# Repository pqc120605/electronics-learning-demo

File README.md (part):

# Mạch Mở — demo học Điện tử, Nhúng và IoT

Mạch Mở là website học miễn phí cho người mới. Khách có thể xem bài học, khám phá mô hình mạch 3D tương tác và thử đổi nhịp LED trong bài ESP32 mà không cần tài khoản. Khu `/admin` dành cho founder để xem thống kê phiên truy cập và tương tác.

## Trang công khai và không gian học

- `/` là trang giới thiệu thế giới điện tử và các tính năng của Mạch Mở.
- `/app` là dashboard học tập dành cho khách, dẫn tới bài học, thư viện board/linh kiện, bàn lắp mạch, chủ đề, công cụ và dự án đang có.
- App workspace là một bề mặt guest-first chạy chung SPA React/Vite với website. Đây chưa phải native app. Service worker cache app shell cùng các JS/CSS đã tải để mở lại một số route khi offline; không cache model 3D lớn, firmware hay API, và chưa có đồng bộ offline.
- Bản đồ sản phẩm Web/App, ranh giới dữ liệu, simulator providers, công cụ GitHub đã khảo sát và lộ trình nền tảng được mô tả trong [`docs/mach-mo-final-web-app-framework.md`](../docs/mach-mo-final-web-app-framework.md).
- Route chuẩn nằm trong `src/data/productRoutes.ts`; feature, trạng thái và nhãn menu dùng chung nằm ở `src/data/productFeatureRegistry.ts`. URL legacy như `/boards` và `/build` vẫn được giữ để tương thích; các đường dẫn app có namespace `/app/...`.
- Hợp đồng chuẩn hóa cho simulation provider nằm tại `src/simulation/contracts.ts`. Các bài học dùng interpreter giáo dục giới hạn trong `src/lib/simulationProviders.ts`; công cụ SPICE dùng `eecircuit-engine`/ngspice WASM trong Web Worker. Workspace có handoff cho subset analog khi dây, node và trị số thỏa mapping hỗ trợ; compiler từ chối MCU/GPIO và phần tử chưa có model. Đây không phải chuyển đổi mọi bài/schematic, không lấy copper PCB làm netlist và không thay provider firmware.
- Luồng CAD có báo cáo đối chiếu tất cả chân có net trong KiCad schematic với PCB IPC-D-356 theo ref/pin và nhóm kết nối; giữ rõ chân NC và bỏ qua record via khi đếm chân. Sau đó, đường tạo netlist SPICE vẫn chỉ ánh xạ R/C/L/V hỗ trợ và yêu cầu loại trừ tường minh phần tử khác. Xem [hướng dẫn nhập KiCad vào SPICE](docs/kicad-to-spice-import.md); đối chiếu CAD không xác nhận file cùng revision hoặc board sản xuất, và PCB đơn lẻ không tự trở thành mô hình điện.
- Các URL chức năng hiện tại như `/learn/esp32-led`, `/boards`, `/components`, `/build`, `/topics`, `/projects` và `/tools/firmware-hex` vẫn dùng trực tiếp được.
- Dashboard `/app` và trang `/topics` hiển thị lộ trình 4 chặng gồm đủ 11 bài (`src/data/learningPath.ts`); bài LED mở trang dài `/learn/esp32-led`, 10 bài còn lại mở trang chuẩn bị `/learn/<id>` với mục tiêu, board, bảng chân, vật tư và mức mô phỏng trước khi vào phòng thử. Thứ tự này cũng quyết định "bài tiếp theo" trong phòng thử. Sơ đồ nguyên lý có danh sách net nối dây; chọn net tô sáng các kết nối tương ứng trên schematic và cảnh lắp. Net ở đây chỉ là topology workspace, không phải ERC, kết quả điện hay copper của PCB tham chiếu. Board profile hiển thị các link tài liệu/ảnh/CAD được khai báo cho đúng mẫu và revision; link nguồn là bằng chứng tham khảo, không xác minh board vật lý người học đang cầm. Bài vừa mở và checklist tự xác nhận của bài LED được lưu cục bộ; đây không phải tiến độ kỹ năng đã xác minh và không đồng bộ tài khoản.
- Cả 11 bài thực hành đều có deep link `?lesson=<id>`, ví dụ `/build?lesson=button-led&guided=1`; khi mở từ `/app`, liên kết nội bộ giữ namespace app. Link bài mở phiên riêng theo tab trong `sessionStorage`, tiếp tục bản nháp của phiên nếu có và không thay workspace `/build` trong `localStorage`. Link `?board=` chỉ đề xuất đổi board khi đã có workspace.
- Công cụ **Kiểm tra firmware HEX** đọc tệp Intel HEX ngay trong trình duyệt, kiểm tra checksum/địa chỉ/kích thước và hiển thị các vùng dữ liệu. Có firmware assembly mẫu và HEX do Arduino IDE 2.3.10 + Arduino AVR Boards 1.8.8 biên dịch từ sketch Uno; AVR8js cho chọn Uno R3 hoặc Nano classic, yêu cầu xác nhận target ATmega328P và chạy tối đa một giây để quan sát GPIO D13/PB5. Tệp người dùng chọn không tải lên máy chủ; target không nhận dạng tự động; web không compile sketch Arduino hay upload, và các board MCU khác chưa được hỗ trợ.
- Trong workspace `/build`, panel **Kết quả đến từ đâu?** phân biệt trace của mô hình bài học với lần chạy HEX AVR8js và waveform trả về từ SPICE. Chế độ HEX là tùy chọn riêng, chỉ nhận Uno R3/Nano classic ATmega328P sau khi người dùng xác nhận target; chỉ hiển thị D13/PB5 và UART0, không ánh xạ lên LED ngoài trên canvas. Kết quả SPICE chỉ quay lại cùng revision workspace trong phiên tab; sửa board, bài, code hoặc dây sẽ dừng/loại kết quả cũ. Đây là quan sát từ provider riêng, không phải đồng mô phỏng firmware–SPICE hay điện áp đo trên board.
- Web manifest cung cấp tên ứng dụng, màu giao diện, biểu tượng và điểm mở `/app`. Tùy trình duyệt và thiết bị, người dùng có thể cài website như một ứng dụng web.
- Cache offline hiện chỉ giữ app shell và tài nguyên cùng origin đã tải. Lần đầu cần có mạng để cài cache; engine SPICE lớn được tải khi mở/chạy công cụ và khả năng dùng offline phụ thuộc cache của trình duyệt. Chưa có tài khoản học viên hay chạy firmware MCU tổng quát.

## Chạy trên máy

Yêu cầu Node.js tương thích với Vite 8.

```powershell
cd D:\StartupOS\electronics-learning-demo
npm.cmd install
npm.cmd run dev -- --host 127.0.0.1 --port 5173 --strictPort --open /build
```

Lệnh luôn dùng `http://127.0.0.1:5173/build`; nếu cổng 5173 đang bận, Vite báo lỗi thay vì âm thầm chuyển sang cổng khác. Đóng cửa sổ terminal đang chạy một bản Mach Mở cũ rồi thử lại. Giữ terminal mở khi dùng web; dừng server bằng `Ctrl+C`.

Trên Windows, có thể chạy `start-demo.cmd` bằng cách nhấp đúp. Script dùng `npm.cmd` để tránh lỗi PowerShell chặn `npm.ps1`, rồi mở workspace `/build` ở cổng cố định. Giữ cửa sổ terminal mở trong lúc dùng; đóng server bằng `Ctrl+C`.

`npm.cmd run build` chạy cổng kiểm tra quyền phân phối trước khi tạo bản production; hiện sẽ bị chặn cho đến khi provenance của ngspice WASM được xác minh. Dùng `npm.cmd run build:local` chỉ để kiểm tra nội bộ; kết quả vẫn chứa WASM và không được phát hành hay tải lên hosting. Xem bản build nội bộ bằng `npm.cmd run preview`.

Kiểm tra kiểu bằng `npm.cmd run typecheck`. Chạy smoke test trước khi thay đổi curriculum, parser hoặc topology bằng `npm.cmd test`. Bộ test chạy qua Node test runner và Vite SSR, không cần cổng localhost; nó kiểm tra dữ liệu bài/board, code mẫu, topology preset của cả mười một bài, một số luật nối mạch và việc biên dịch các page module. Nó chưa tự thao tác UI trên trình duyệt.

Để rà model board, dùng `npm.cmd run audit:board-models` cho hotspot/anchor/scene bounds và `npm.cmd run audit:board-model-geometry` để so mesh thân PCB từ STEP đã ghim SHA-256 với node PCB tách riêng trong GLB (hiện có 8 cặp nguồn). Kết quả CAD-to-CAD không thay thế đo board thật. `npm.cmd run audit:spice-engine` kiểm tra hash/runtime và giải mạch DC mẫu; `npm.cmd run check:public-release` cố ý chặn cho tới khi đủ provenance, inventory và review phân phối ngspice WASM.

## Cấu hình Supabase riêng

Website này cần một Supabase project riêng. Không dùng project, URL, key hoặc dữ liệu của ReTrack. Nội dung học vẫn chạy nếu chưa cấu hình Supabase; khi chưa cấu hình, admin hiển thị hướng dẫn thiết lập và thống kê chưa khả dụng.

1. Tạo Supabase project dành riêng cho website.
2. Chạy lần lượt `supabase/migrations/0001_analytics_and_admin.sql` và `supabase/migrations/0002_analytics_rate_limit.sql` trong SQL Editor. Migration thứ hai thêm sự kiện chạy bài và giới hạn tốc độ theo mã phiên.
3. Trong Authentication → Settings, tắt đăng ký public. Trong Authentication → Users, tạo user founder với email và mật khẩu của bạn.
4. Lấy UUID của user trong Authentication → Users. Trong SQL Editor, cấp role admin cho đúng UUID:

   ```sql
   insert into public.site_admins (user_id)
   values ('DAN_UUID_USER_FOUNDER_VAO_DAY');
   ```

   Không thêm form đăng ký hoặc luồng tự cấp role vào website.
5. Sao chép `.env.example` thành `.env.local`, điền URL project và publishable/anon key. Chỉ dùng key công khai trong trình duyệt; không đưa service-role key vào `VITE_*` hay mã nguồn.
6. Khởi động lại dev server và mở `/admin` để đăng nhập.

Analytics chỉ ghi mã phiên ngẫu nhiên theo tab, loại sự kiện trong allowlist, đường dẫn, component tùy chọn và thời gian máy chủ. Số phiên là ước tính, không phải số người thật được xác minh. Nhà cung cấp backend có thể xử lý metadata kỹ thuật để vận hành.

## Giới hạn demo

- View "Lắp mạch · 3D" trong phòng thử dựng cảnh từ GLB thật, có chọn linh kiện, callout, panel thông tin và luồng logic minh họa. Nhãn HIGH/LOW và hướng lấy từ chương trình và sơ đồ bài học, không phải điện áp hay dòng đo được. Linh kiện giữ đúng tỉ lệ và được tự xếp lên breadboard; chỉ các chân cùng net mới chung một dải. Đây là cách lắp gợi ý, chưa kiểm tra trên mạch thật. Chân của model tham số và Pico là vị trí minh họa.

- Trang Linh kiện và phòng thử hiển thị minh họa/mesh 3D theo hồ sơ từng linh kiện; model package KiCad là vỏ chuẩn, còn model tham số chỉ là hình khối giáo dục. Board Adafruit QT Py ESP32-C3 Rev B #5405 và Feather ESP32-S3 PID #5323 có viewer CAD riêng theo nguồn hãng. Feather hiển thị cả footprint chưa có mesh và để các mesh không đối chiếu được ở trạng thái chưa định danh. Chi tiết, nguồn và giấy phép ở `docs/component-model-registry.md` và `docs/board-model-sourcing.md`.

- Bài ESP32 có hai cảnh 3D: PCB theo thiết kế ESP32 Dev Kit Clone 30 chân có schematic/netlist, và cảnh lắp mạch học tập gồm board, breadboard, LED, điện trở 220 Ω cùng dây jumper. Chọn linh kiện để xem vai trò, net/pad liên quan và lưu ý an toàn. Thiết kế này đo khoảng 47,06 × 29,23 mm; không đại diện cho mọi board bán dưới tên DevKit V1. Phần breadboard và linh kiện ngoài là hình học minh họa, không phải netlist hay mô phỏng điện.
- Viewer dùng WebGL2 và đọc profile GLB KiCad của asset mẫu. Mô hình chỉ thể hiện hình học, không mô phỏng điện áp/dòng điện hay chạy firmware. Hiệu ứng LED nhấp nháy trong viewer bài học chỉ là phản hồi hình ảnh.
- PCB, schematic, thông tin nguồn và hướng dẫn tái tạo model nằm trong `assets/boards/esp32-devkit-v1-30pin/`; GLB phục vụ web nằm trong `public/models/`. Sau khi xuất lại PCB GLB bằng KiCad, chạy `python assets/boards/esp32-devkit-v1-30pin/compose_led_assembly.py` để dựng lại cảnh lắp ráp. U3 CP2102 dùng vỏ QFN KiCad cùng kích thước, không có marking mặt chip.
- Web không biên dịch code hoặc nạp code qua USB. AVR8js là runner giới hạn cho ATmega328P trên Uno R3/Nano classic, nhận firmware HEX đã biên dịch và quan sát D13/ngoại vi cơ bản; không phải mô phỏng điện tổng quát hay hỗ trợ ESP32/Pico/STM32.
- Các model Arduino Uno/Nano/Mega trên web đã được thay bằng hình học PCB từ CAD board tham chiếu, kèm package 3D cho MCU, một số linh kiện thụ động, LED và header. CAD nguồn, attribution, giới hạn và cách xuất lại ở `assets/boards/arduino-reference/README.md`.
- Project chưa đọc được không bị xóa khi lưu; trang Dự án cho tải bản sao phục hồi. Kiểm kê asset và trạng thái Git nằm ở `docs/asset-and-repo-inventory.md`.
- Bản đầu chưa có tài khoản học viên, đồng bộ hoặc xác minh tiến độ học tập, thanh toán hay cửa hàng kit. Lịch sử bài vừa mở và checklist tự xác nhận, project và bản nháp workspace được lưu cục bộ trên thiết bị.
- Bài mẫu nêu rõ loại board và giả định chân GPIO; hãy đối chiếu pinout của board thực tế trước khi nối dây.

### Cách đọc mức độ mô phỏng và độ tin cậy

- **Mô phỏng hành vi cơ bản**: parser chỉ hiểu một tập câu lệnh được liệt kê trong bài. Nó chuyển code thuộc tập đó thành trạng thái/luồng minh họa; không biên dịch hay chạy firmware.
- **Minh họa khái niệm**: hoạt động theo kịch bản định sẵn; code mẫu không được thực thi.
- **Mô hình tham chiếu · CAD theo revision**: hình học được dựng từ bộ CAD/revision đã ghi nguồn. Nhãn này không xác nhận board clone đang bán có cùng layout, BOM hay linh kiện thực tế.
- **Alias học tập / suy luận từ CAD**: vị trí/chân hoặc package chưa được xác minh hoàn toàn. Các linh kiện rời trong bàn lắp có thể là hình học giáo dục tham số, không phải model nhà sản xuất.

Danh mục `/boards` ghi revision, nguồn và trạng thái viewer; `/components` phân biệt linh kiện có trong topology bài mẫu, chỉ hiển thị và chỉ tra cứu. Trang thư viện board và trang học hiển thị provenance của model: trạng thái, revision, nguồn, giấy phép/ghi công, độ tin cậy và các điểm còn thiếu. Không nên hiểu “có model 3D” là đã xác thực mọi linh kiện hoặc mô phỏng điện chính xác.

## Bộ công cụ

- `/tools/electronics-calculators` và `/app/tools/calculators`: bộ tính điện trở LED, bộ chia áp ADC, pull-up I²C và mạch RC. Mỗi kết quả hợp lệ có thể mở netlist tương đương trong SPICE. Trong workspace, tab **Schematic**, **Lắp mạch 3D** và **PCB** có thể gửi topology dây tường minh cùng R/C/LED/diode/LDR và trị số đã khai báo sang bộ biên dịch analog; yêu cầu GND, nguồn và các chân phải nối đủ. Board MCU, code/firmware, copper CAD, ký sinh PCB và linh kiện không có mapping đều bị loại hoặc chặn với lý do cụ thể. Đây là circuit subset theo topology workspace, không phải mô phỏng toàn board. Kết quả cần đối chiếu datasheet trước khi lắp thật.
- `/tools/spice` và `/app/tools/spice`: netlist analog chạy bằng ngspice WASM trong Web Worker của trình duyệt. Có ví dụ DC, RC transient, diode; netlist tối đa 16 kB/160 dòng, tối đa 20.000 điểm ước tính và giới hạn kết quả solver 20.000 điểm, timeout 30 giây; xem đồ thị/bảng và xuất CSV. Hỗ trợ có giới hạn R/C/L, V/I, diode/BJT/MOSFET với model số khai báo trực tiếp; chỉ `.op`, `.tran`, `.ac`, `.dc`. Ngoài handoff từ workspace, có thể nhập **XML netlist xuất từ KiCad Eeschema**: chỉ R/C/L và nguồn V DC có trị số tĩnh được giữ; linh kiện khác phải loại trừ bằng thao tác rõ ràng, nguồn/chân GND cần có. File `.kicad_sch`/`.kicad_pcb`, copper, parasitic, IC/MCU và firmware không tự chuyển đổi. Không nhận file/include/control, không chạy firmware MCU và không phải công cụ xác nhận an toàn/phần cứng. Engine WASM tải riêng khoảng 6,1 MB khi mở công cụ.
- Engine đóng gói từ `eecircuit-engine` 1.8.0; giấy phép MIT của wrapper được kèm ở `public/licenses/eecircuit-engine-MIT.txt`. **Quyền tái phân phối công khai của đúng ngspice WASM hiện chưa được xác minh**: source commit, build recipe và inventory thành phần linked còn thiếu dù artifact đang được phục vụ trong `public/`. Xem [provenance](public/licenses/spice-engine-provenance.json), [notice](public/licenses/NGSPICE-NOTICE.txt) và [ngspice COPYING](https://github.com/ngspice/ngspice/blob/master/COPYING).
- `postinstall` chạy `scripts/prepare-spice-engine.mjs`: tách WASM 6,1 MB khỏi bundle và bỏ các model-card foundry đóng gói sẵn mà giao diện không nhận qua `.include`. Các model người dùng khai báo trực tiếp trong netlist vẫn do solver xử lý. Script khóa phiên bản engine 1.8.0 và dừng nếu cấu trúc upstream thay đổi; license và thông báo của package vẫn được giữ.
- `/app/classroom-kits`: kế hoạch lớp/kit cục bộ, chọn board và revision tham chiếu, 1–100 trạm, bài học, số lượng kit, lưu ý an toàn, in phiếu, xuất CSV/JSON và nhập lại gói đã kiểm tra allowlist. Gói chia sẻ thủ công kèm link bài, nhãn năng lực mô phỏng, thông tin board/revision, nguồn board và ghi chú an toàn; chưa có upload/cloud, tài khoản lớp, bảng tin hay kiểm duyệt cộng đồng. Không thu dữ liệu học sinh.

## Thư viện board và bài học lập trình

- Trang Khám phá có tìm kiếm và lọc theo ESP, Arduino, STM32; có thể chọn tối đa ba board để so sánh MCU, revision, điện áp logic, ngoại vi, mục tiêu phù hợp, điểm đánh đổi và trạng thái model. Bảng cảnh báo khi mức logic khác nhau, có link nguồn, bỏ từng board và xóa lựa chọn. Thông tin preview luôn đi kèm nguồn và trạng thái xác minh.
- Bài LED có chế độ khối cho người mới, tạo code C++ từ các khối GPIO/chờ, và chế độ C++ riêng để tự luyện. Bản nháp code được giữ khi đổi chế độ; chỉ cú pháp thuộc tập con được hỗ trợ mới chuyển thành luồng minh họa. Cú pháp khác được giữ nguyên và tắt luồng, không chạy code trong trình duyệt.
- Luồng hoạt động chỉ minh họa câu lệnh, GPIO và trạng thái LED theo từng bước; không mô phỏng firmware, điện học hoặc thời gian thực.
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
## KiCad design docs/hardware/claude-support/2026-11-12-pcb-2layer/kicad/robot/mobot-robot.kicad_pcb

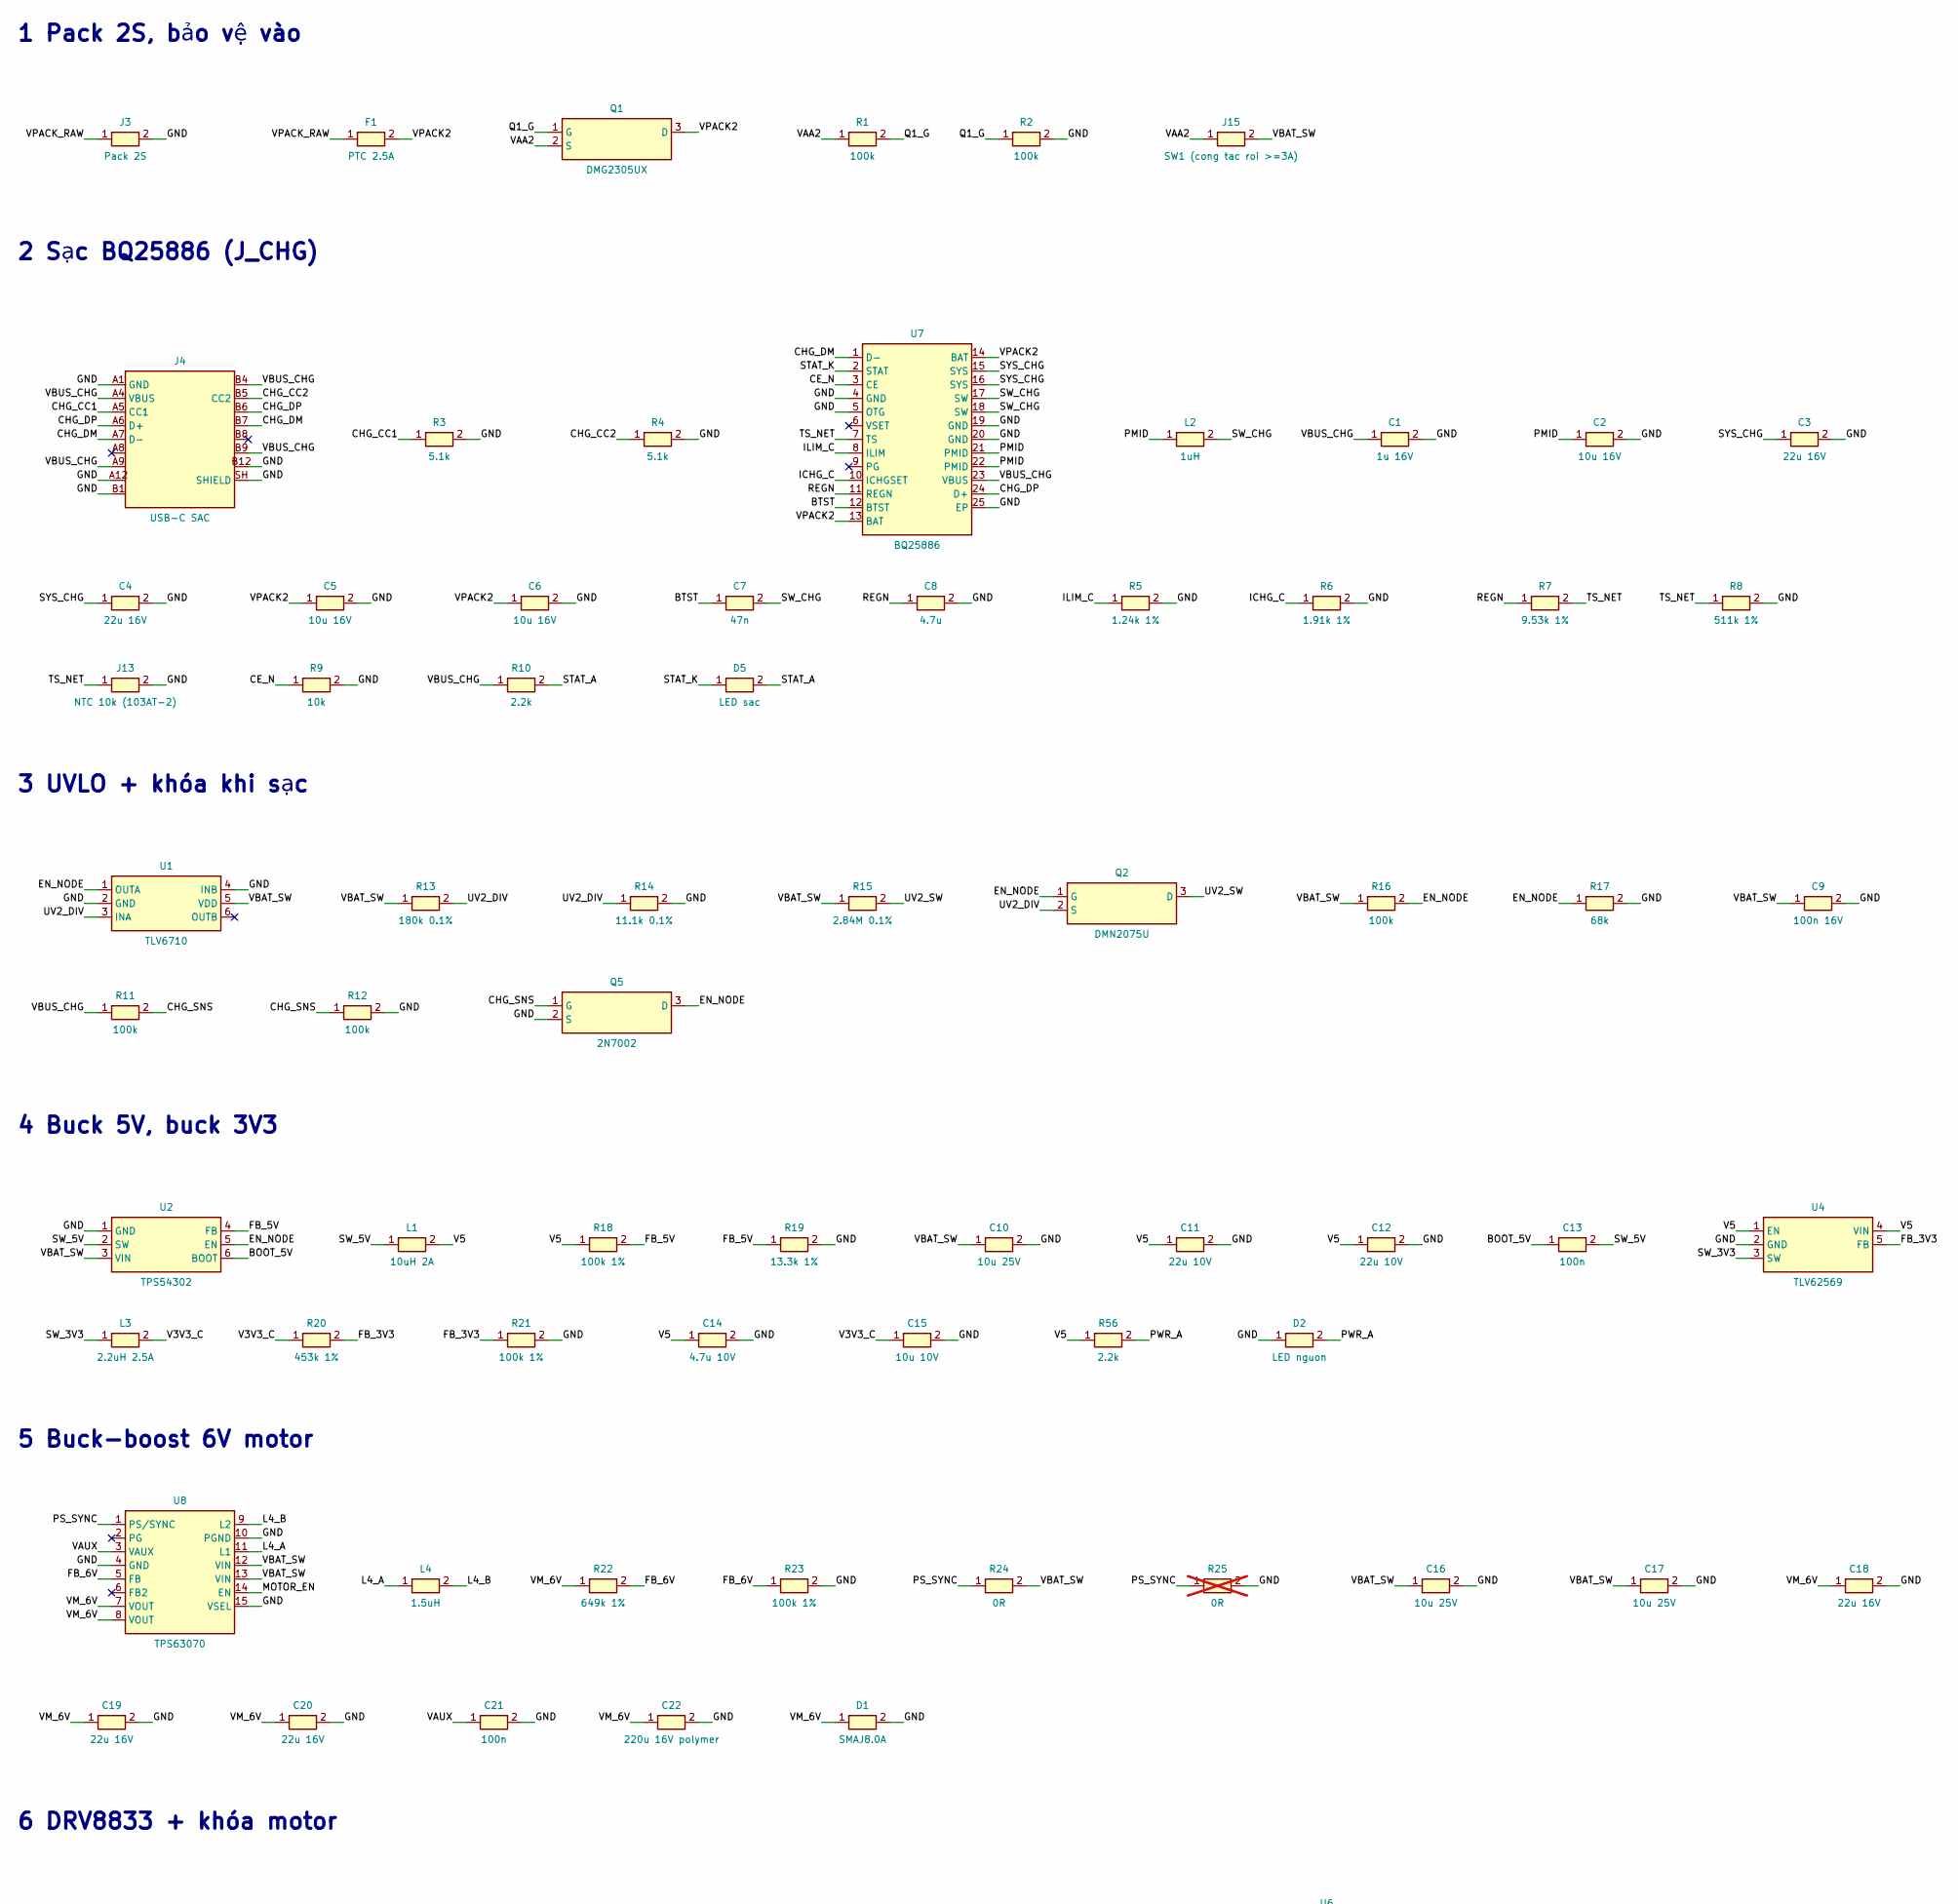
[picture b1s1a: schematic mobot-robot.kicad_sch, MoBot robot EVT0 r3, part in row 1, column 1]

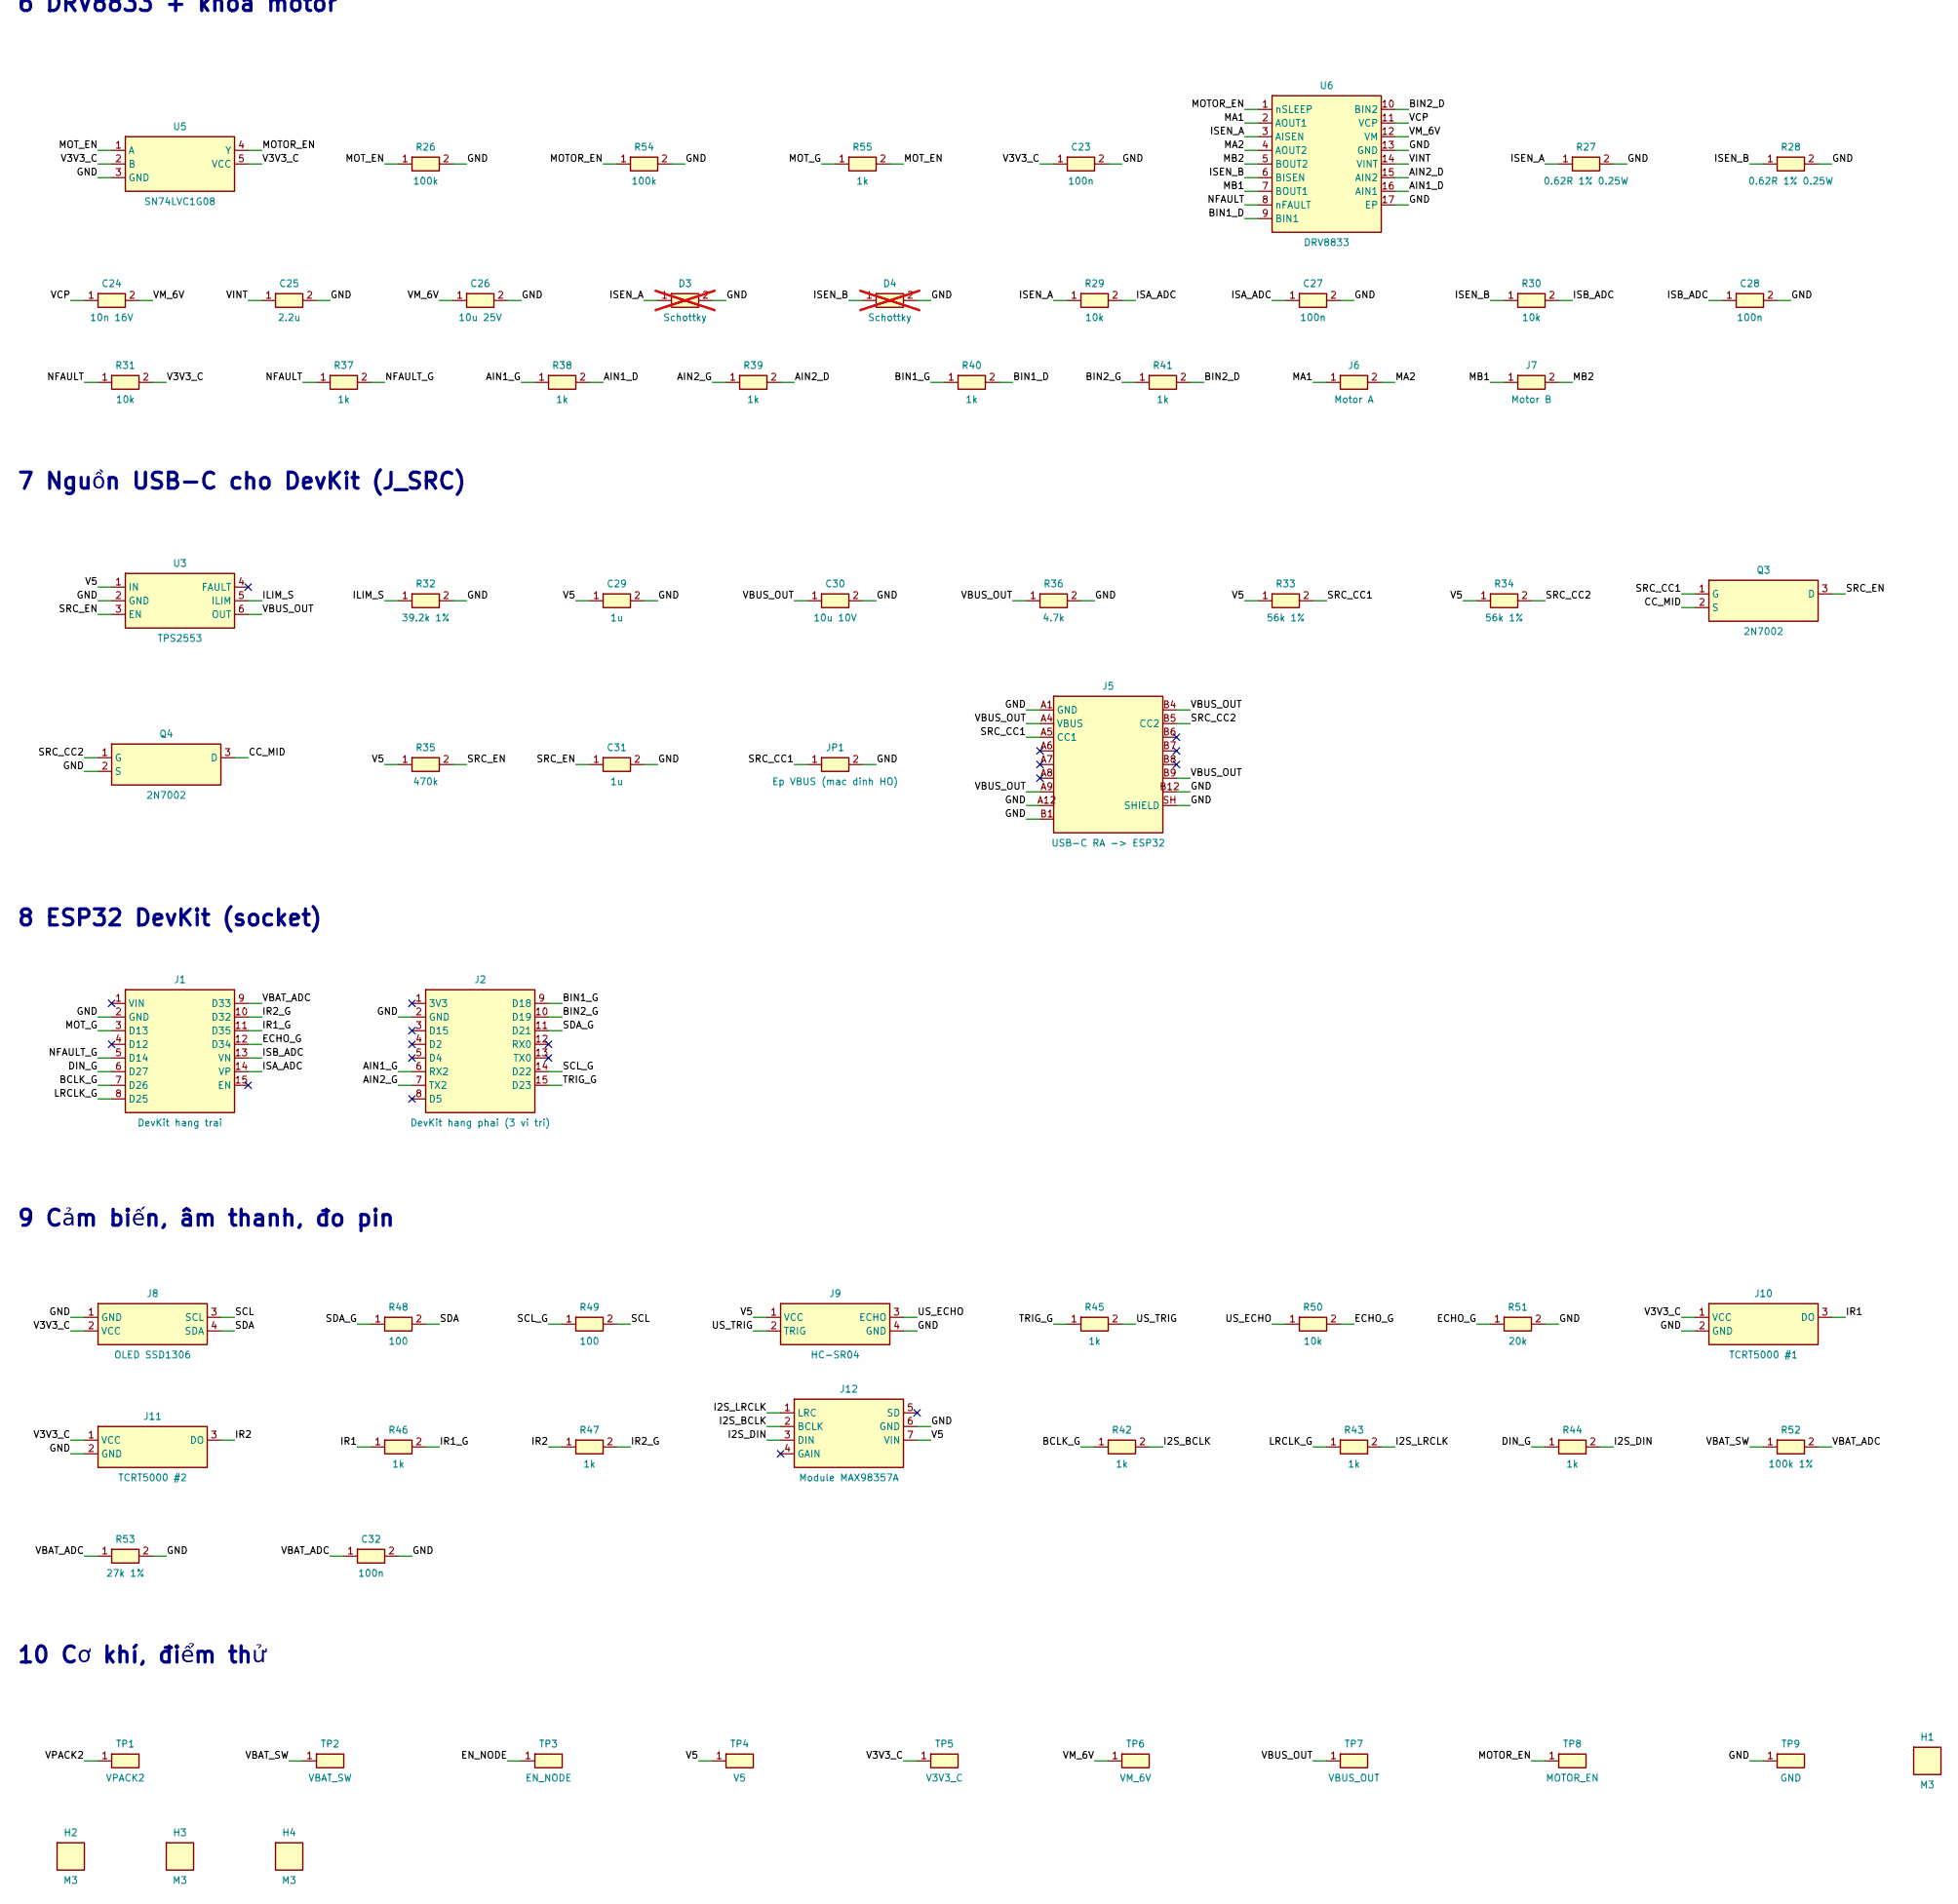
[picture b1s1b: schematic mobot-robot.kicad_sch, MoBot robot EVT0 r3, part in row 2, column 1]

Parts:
C1: 1u 16V; C_0603_1608Metric
C2, C5, C6: 10u 16V; C_0805_2012Metric
C3, C4, C18, C19, C20: 22u 16V; C_0805_2012Metric
C7: 47n; C_0603_1608Metric
C8: 4.7u; C_0603_1608Metric
C9: 100n 16V; C_0603_1608Metric
C10, C16, C17, C26: 10u 25V; C_0805_2012Metric
C11, C12: 22u 10V; C_0805_2012Metric
C13, C21, C23, C27, C28, C32: 100n; C_0603_1608Metric
C14: 4.7u 10V; C_0805_2012Metric
C15, C30: 10u 10V; C_0805_2012Metric
C22: 220u 16V polymer; CP_Elec_8x10
C24: 10n 16V; C_0603_1608Metric
C25: 2.2u; C_0603_1608Metric
C29, C31: 1u; C_0603_1608Metric
D1: SMAJ8.0A; D_SMA; MPN SMAJ8.0A
D2: LED nguon; LED_0603_1608Metric
D3, D4: Schottky; D_SOD-323; not fitted
D5: LED sac; LED_0603_1608Metric
F1: PTC 2.5A; Fuse_1812_4532Metric; MPN MF-MSMF250/16X
H1, H2, H3, H4: M3; MountingHole_3.2mm_M3
J1: DevKit hang trai; PinSocket_1x15_P2.54mm_Vertical
J2: DevKit hang phai (3 vi tri); PinSocket_1x15_Alt3Rows_22.86_25.40_27.94
J3: Pack 2S; JST_XH_B2B-XH-A_1x02_P2.50mm_Vertical; MPN B2B-XH-A
J4: USB-C SAC; USB_C_Receptacle_GCT_USB4105-xx-A_16P_TopMnt_Horizontal; MPN USB4105-GF-A
J5: USB-C RA -> ESP32; USB_C_Receptacle_GCT_USB4105-xx-A_16P_TopMnt_Horizontal; MPN USB4105-GF-A
J6: Motor A; JST_XH_B2B-XH-A_1x02_P2.50mm_Vertical; MPN B2B-XH-A
J7: Motor B; JST_XH_B2B-XH-A_1x02_P2.50mm_Vertical; MPN B2B-XH-A
J8: OLED SSD1306; PinSocket_1x04_P2.54mm_Vertical
J9: HC-SR04; PinSocket_1x04_P2.54mm_Vertical
J10: TCRT5000 #1; PinHeader_1x03_P2.54mm_Vertical
J11: TCRT5000 #2; PinHeader_1x03_P2.54mm_Vertical
J12: Module MAX98357A; PinSocket_1x07_P2.54mm_Vertical
J13: NTC 10k (103AT-2); JST_PH_B2B-PH-K_1x02_P2.00mm_Vertical; MPN B2B-PH-K-S
J15: SW1 (cong tac roi >=3A); JST_XH_B2B-XH-A_1x02_P2.50mm_Vertical; MPN B2B-XH-A
JP1: Ep VBUS (mac dinh HO); SolderJumper-2_P1.3mm_Open_RoundedPad1.0x1.5mm
L1: 10uH 2A; L_Taiyo-Yuden_NR-50xx
L2: 1uH; L_Vishay_IHLP-2525; MPN IHLP2525CZER1R0M01
L3: 2.2uH 2.5A; L_Changjiang_FNR4030S
L4: 1.5uH; L_Changjiang_FNR4020S; MPN XFL4020-152ME
Q1: DMG2305UX; SOT-23; MPN DMG2305UX-7
Q2: DMN2075U; SOT-23; MPN DMN2075U-7
Q3, Q4, Q5: 2N7002; SOT-23; MPN 2N7002
R1, R2, R11, R12, R16, R26, R54: 100k; R_0603_1608Metric
R3, R4: 5.1k; R_0603_1608Metric
R5: 1.24k 1%; R_0603_1608Metric
R6: 1.91k 1%; R_0603_1608Metric
R7: 9.53k 1%; R_0603_1608Metric
R8: 511k 1%; R_0603_1608Metric
R9, R29, R30, R31, R50: 10k; R_0603_1608Metric
R10, R56: 2.2k; R_0603_1608Metric
R13: 180k 0.1%; R_0603_1608Metric
R14: 11.1k 0.1%; R_0603_1608Metric
R15: 2.84M 0.1%; R_0603_1608Metric
R17: 68k; R_0603_1608Metric
R18, R21, R23, R52: 100k 1%; R_0603_1608Metric
R19: 13.3k 1%; R_0603_1608Metric
R20: 453k 1%; R_0603_1608Metric
R22: 649k 1%; R_0603_1608Metric
R24: 0R; R_0603_1608Metric
R25: 0R; R_0603_1608Metric; not fitted
R27, R28: 0.62R 1% 0.25W; R_1206_3216Metric
R32: 39.2k 1%; R_0603_1608Metric
R33, R34: 56k 1%; R_0603_1608Metric
R35: 470k; R_0603_1608Metric
R36: 4.7k; R_0603_1608Metric
R37, R38, R39, R40, R41, R42, R43, R44, R45, R46, R47, R55: 1k; R_0603_1608Metric
R48, R49: 100; R_0603_1608Metric
R51: 20k; R_0603_1608Metric
R53: 27k 1%; R_0603_1608Metric
TP1: VPACK2; TestPoint_Pad_D1.5mm
TP2: VBAT_SW; TestPoint_Pad_D1.5mm
TP3: EN_NODE; TestPoint_Pad_D1.5mm
TP4: V5; TestPoint_Pad_D1.5mm
TP5: V3V3_C; TestPoint_Pad_D1.5mm
TP6: VM_6V; TestPoint_Pad_D1.5mm
TP7: VBUS_OUT; TestPoint_Pad_D1.5mm
TP8: MOTOR_EN; TestPoint_Pad_D1.5mm
TP9: GND; TestPoint_Pad_D1.5mm
U1: TLV6710; TSOT-23-6; MPN TLV6710DDCR
U2: TPS54302; SOT-23-6; MPN TPS54302DDCR
U3: TPS2553; SOT-23-6; MPN TPS2553DBVR
U4: TLV62569; SOT-23-5; MPN TLV62569DBVR
U5: SN74LVC1G08; SOT-23-5; MPN SN74LVC1G08DBVR
U6: DRV8833; HTSSOP-16-1EP_4.4x5mm_P0.65mm_EP3.4x5mm_Mask2.46x2.31mm_The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; MPN DRV8833PWPR
U7: BQ25886; VQFN-24-1EP_4x4mm_P0.5mm_EP2.45x2.45mm; MPN BQ25886RGER
U8: TPS63070; Texas_RNM0015A_VQFN-15_2.5x3mm; MPN TPS63070RNMR

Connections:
/AIN1_D: R38.2, U6.16 (AIN1)
/AIN1_G: J2.6 (RX2), R38.1
/AIN2_D: R39.2, U6.15 (AIN2)
/AIN2_G: J2.7 (TX2), R39.1
/BCLK_G: J1.7 (D26), R42.1
/BIN1_D: R40.2, U6.9 (BIN1)
/BIN1_G: J2.9 (D18), R40.1
/BIN2_D: R41.2, U6.10 (BIN2)
/BIN2_G: J2.10 (D19), R41.1
/BOOT_5V: C13.1, U2.6 (BOOT)
/BTST: C7.1, U7.12 (BTST)
/CC_MID: Q3.2 (S), Q4.3 (D)
/CE_N: R9.1, U7.3 (CE)
/CHG_CC1: J4.A5 (CC1), R3.1
/CHG_CC2: J4.B5 (CC2), R4.1
/CHG_DM: J4.A7 (D-), J4.B7, U7.1 (D-)
/CHG_DP: J4.A6 (D+), J4.B6, U7.24 (D+)
/CHG_SNS: Q5.1 (G), R11.2, R12.1
/DIN_G: J1.6 (D27), R44.1
/ECHO_G: J1.12 (D34), R50.2, R51.1
/EN_NODE: Q2.1 (G), Q5.3 (D), R16.2, R17.1, TP3.1, U1.1 (OUTA), U2.5 (EN)
/FB_3V3: R20.2, R21.1, U4.5 (FB)
/FB_5V: R18.2, R19.1, U2.4 (FB)
/FB_6V: R22.2, R23.1, U8.5 (FB)
/GND: C1.2, C2.2, C3.2, C4.2, C5.2, C6.2, C8.2, C9.2, C10.2, C11.2, C12.2, C14.2, C15.2, C16.2, C17.2, C18.2, C19.2, C20.2, C21.2, C22.2 (-), C23.2, C25.2, C26.2, C27.2, C28.2, C29.2, C30.2, C31.2, C32.2, D1.2 (A), D2.1 (K), D3.2 (A), D4.2 (A), J1.2 (GND), J2.2 (GND), J3.2 (-), J4.A1 (GND), J4.A12, J4.B1, J4.B12, J4.SH (SHIELD), J5.A1 (GND), J5.A12, J5.B1, J5.B12, J5.SH (SHIELD), J8.1 (GND), J9.4 (GND), J10.2 (GND), J11.2 (GND), J12.6 (GND), J13.2, JP1.2, Q4.2 (S), Q5.2 (S), R2.2, R3.2, R4.2, R5.2, R6.2, R8.2, R9.2, R12.2, R14.2, R17.2, R19.2, R21.2, R23.2, R25.2, R26.2, R27.2, R28.2, R32.2, R36.2, R51.2, R53.2, R54.2, TP9.1, U1.2 (GND), U1.4 (INB), U2.1 (GND), U3.2 (GND), U4.2 (GND), U5.3 (GND), U6.13 (GND), U6.17 (EP), U7.4 (GND), U7.5 (OTG), U7.19 (GND), U7.20 (GND), U7.25 (EP), U8.4 (GND), U8.10 (PGND), U8.15 (VSEL)
/I2S_BCLK: J12.2 (BCLK), R42.2
/I2S_DIN: J12.3 (DIN), R44.2
/I2S_LRCLK: J12.1 (LRC), R43.2
/ICHG_C: R6.1, U7.10 (ICHGSET)
/ILIM_C: R5.1, U7.8 (ILIM)
/ILIM_S: R32.1, U3.5 (ILIM)
/IR1: J10.3 (DO), R46.1
/IR1_G: J1.11 (D35), R46.2
/IR2: J11.3 (DO), R47.1
/IR2_G: J1.10 (D32), R47.2
/ISA_ADC: C27.1, J1.14 (VP), R29.2
/ISB_ADC: C28.1, J1.13 (VN), R30.2
/ISEN_A: D3.1 (K), R27.1, R29.1, U6.3 (AISEN)
/ISEN_B: D4.1 (K), R28.1, R30.1, U6.6 (BISEN)
/L4_A: L4.1, U8.11 (L1)
/L4_B: L4.2, U8.9 (L2)
/LRCLK_G: J1.8 (D25), R43.1
/MA1: J6.1, U6.2 (AOUT1)
/MA2: J6.2, U6.4 (AOUT2)
/MB1: J7.1, U6.7 (BOUT1)
/MB2: J7.2, U6.5 (BOUT2)
/MOTOR_EN: R54.1, TP8.1, U5.4 (Y), U6.1 (nSLEEP), U8.14 (EN)
/MOT_EN: R26.1, R55.2, U5.1 (A)
/MOT_G: J1.3 (D13), R55.1
/NFAULT: R31.1, R37.1, U6.8 (nFAULT)
/NFAULT_G: J1.5 (D14), R37.2
/PMID: C2.1, L2.1, U7.21 (PMID), U7.22 (PMID)
/PS_SYNC: R24.1, R25.1, U8.1 (PS/SYNC)
/PWR_A: D2.2 (A), R56.2
/Q1_G: Q1.1 (G), R1.2, R2.1
/REGN: C8.1, R7.1, U7.11 (REGN)
/SCL: J8.3 (SCL), R49.2
/SCL_G: J2.14 (D22), R49.1
/SDA: J8.4 (SDA), R48.2
/SDA_G: J2.11 (D21), R48.1
/SRC_CC1: J5.A5 (CC1), JP1.1, Q3.1 (G), R33.2
/SRC_CC2: J5.B5 (CC2), Q4.1 (G), R34.2
/SRC_EN: C31.1, Q3.3 (D), R35.2, U3.3 (EN)
/STAT_A: D5.2 (A), R10.2
/STAT_K: D5.1 (K), U7.2 (STAT)
/SW_3V3: L3.1, U4.3 (SW)
/SW_5V: C13.2, L1.1, U2.2 (SW)
/SW_CHG: C7.2, L2.2, U7.17 (SW), U7.18 (SW)
/SYS_CHG: C3.1, C4.1, U7.15 (SYS), U7.16 (SYS)
/TRIG_G: J2.15 (D23), R45.1
/TS_NET: J13.1, R7.2, R8.1, U7.7 (TS)
/US_ECHO: J9.3 (ECHO), R50.1
/US_TRIG: J9.2 (TRIG), R45.2
/UV2_DIV: Q2.2 (S), R13.2, R14.1, U1.3 (INA)
/UV2_SW: Q2.3 (D), R15.2
/V3V3_C: C15.1, C23.1, J8.2 (VCC), J10.1 (VCC), J11.1 (VCC), L3.2, R20.1, R31.2, TP5.1, U5.2 (B), U5.5 (VCC)
/V5: C11.1, C12.1, C14.1, C29.1, J9.1 (VCC), J12.7 (VIN), L1.2, R18.1, R33.1, R34.1, R35.1, R56.1, TP4.1, U3.1 (IN), U4.1 (EN), U4.4 (VIN)
/VAA2: J15.1 (IN), Q1.2 (S), R1.1
/VAUX: C21.1, U8.3 (VAUX)
/VBAT_ADC: C32.1, J1.9 (D33), R52.2, R53.1
/VBAT_SW: C9.1, C10.1, C16.1, C17.1, J15.2 (OUT), R13.1, R15.1, R16.1, R24.2, R52.1, TP2.1, U1.5 (VDD), U2.3 (VIN), U8.12 (VIN), U8.13 (VIN)
/VBUS_CHG: C1.1, J4.A4 (VBUS), J4.A9, J4.B4, J4.B9, R10.1, R11.1, U7.23 (VBUS)
/VBUS_OUT: C30.1, J5.A4 (VBUS), J5.A9, J5.B4, J5.B9, R36.1, TP7.1, U3.6 (OUT)
/VCP: C24.1, U6.11 (VCP)
/VINT: C25.1, U6.14 (VINT)
/VM_6V: C18.1, C19.1, C20.1, C22.1 (+), C24.2, C26.1, D1.1 (K), R22.1, TP6.1, U6.12 (VM), U8.7 (VOUT), U8.8 (VOUT)
/VPACK2: C5.1, C6.1, F1.2, Q1.3 (D), TP1.1, U7.13 (BAT), U7.14 (BAT)
/VPACK_RAW: F1.1, J3.1 (+)

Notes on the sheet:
1 Pack 2S, bảo vệ vào
2 Sạc BQ25886 (J_CHG)
3 UVLO + khóa khi sạc
4 Buck 5V, buck 3V3
5 Buck-boost 6V motor
6 DRV8833 + khóa motor
7 Nguồn USB-C cho DevKit (J_SRC)
8 ESP32 DevKit (socket)
9 Cảm biến, âm thanh, đo pin
10 Cơ khí, điểm thử

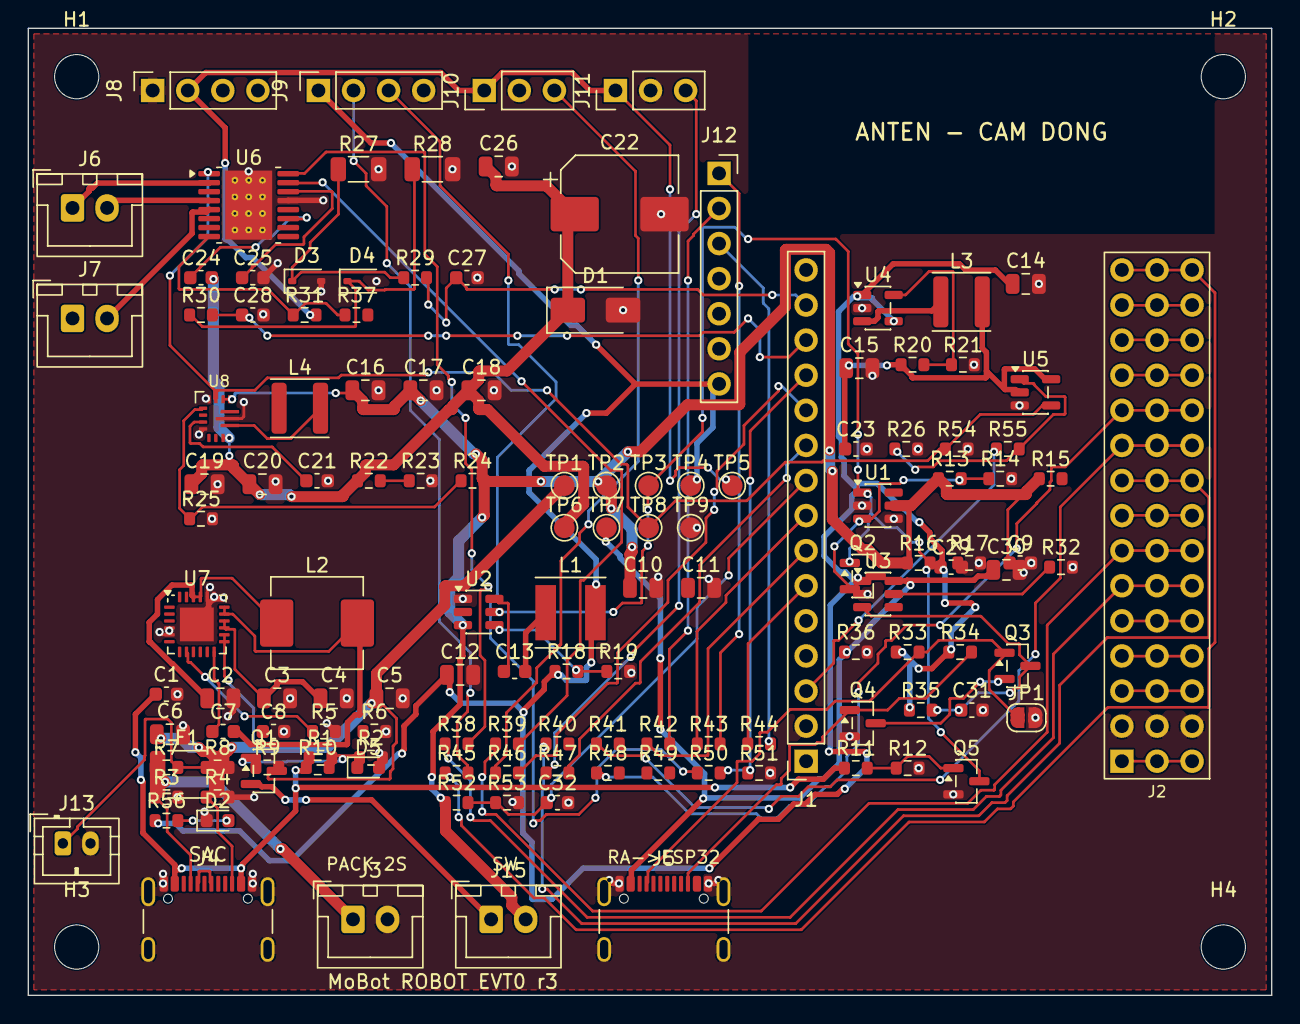
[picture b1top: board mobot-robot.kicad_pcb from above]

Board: 2 copper layers, 90.0 x 70.0 mm, 139 parts (0 on the bottom side), 88 nets.

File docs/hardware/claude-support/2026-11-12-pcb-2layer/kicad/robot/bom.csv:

"Ref","Value","Footprint","MPN","Qty","DNP"
"C1","1u 16V","Capacitor_SMD:C_0603_1608Metric","","1",""
"C2,C5,C6","10u 16V","Capacitor_SMD:C_0805_2012Metric","","3",""
"C3,C4,C18-C20","22u 16V","Capacitor_SMD:C_0805_2012Metric","","5",""
"C7","47n","Capacitor_SMD:C_0603_1608Metric","","1",""
"C8","4.7u","Capacitor_SMD:C_0603_1608Metric","","1",""
"C9","100n 16V","Capacitor_SMD:C_0603_1608Metric","","1",""
"C10,C16,C17,C26","10u 25V","Capacitor_SMD:C_0805_2012Metric","","4",""
"C11,C12","22u 10V","Capacitor_SMD:C_0805_2012Metric","","2",""
"C13,C21,C23,C27,C28,C32","100n","Capacitor_SMD:C_0603_1608Metric","","6",""
"C14","4.7u 10V","Capacitor_SMD:C_0805_2012Metric","","1",""
"C15,C30","10u 10V","Capacitor_SMD:C_0805_2012Metric","","2",""
"C22","220u 16V polymer","Capacitor_SMD:CP_Elec_8x10","","1",""
"C24","10n 16V","Capacitor_SMD:C_0603_1608Metric","","1",""
"C25","2.2u","Capacitor_SMD:C_0603_1608Metric","","1",""
"C29,C31","1u","Capacitor_SMD:C_0603_1608Metric","","2",""
"D1","SMAJ8.0A","Diode_SMD:D_SMA","SMAJ8.0A","1",""
"D2","LED nguon","LED_SMD:LED_0603_1608Metric","","1",""
"D3,D4","Schottky","Diode_SMD:D_SOD-323","","2","DNP"
"D5","LED sac","LED_SMD:LED_0603_1608Metric","","1",""
"F1","PTC 2.5A","Fuse:Fuse_1812_4532Metric","MF-MSMF250/16X","1",""
"J1","DevKit hang trai","Connector_PinSocket_2.54mm:PinSocket_1x15_P2.54mm_Vertical","","1",""
"J2","DevKit hang phai (3 vi tri)","mobot:PinSocket_1x15_Alt3Rows_22.86_25.40_27.94","","1",""
"J3","Pack 2S","Connector_JST:JST_XH_B2B-XH-A_1x02_P2.50mm_Vertical","B2B-XH-A","1",""
"J4","USB-C SAC","Connector_USB:USB_C_Receptacle_GCT_USB4105-xx-A_16P_TopMnt_Horizontal","USB4105-GF-A","1",""
"J5","USB-C RA -> ESP32","Connector_USB:USB_C_Receptacle_GCT_USB4105-xx-A_16P_TopMnt_Horizontal","USB4105-GF-A","1",""
"J6","Motor A","Connector_JST:JST_XH_B2B-XH-A_1x02_P2.50mm_Vertical","B2B-XH-A","1",""
"J7","Motor B","Connector_JST:JST_XH_B2B-XH-A_1x02_P2.50mm_Vertical","B2B-XH-A","1",""
"J8","OLED SSD1306","Connector_PinSocket_2.54mm:PinSocket_1x04_P2.54mm_Vertical","","1",""
"J9","HC-SR04","Connector_PinSocket_2.54mm:PinSocket_1x04_P2.54mm_Vertical","","1",""
"J10","TCRT5000 #1","Connector_PinHeader_2.54mm:PinHeader_1x03_P2.54mm_Vertical","","1",""
"J11","TCRT5000 #2","Connector_PinHeader_2.54mm:PinHeader_1x03_P2.54mm_Vertical","","1",""
"J12","Module MAX98357A","Connector_PinSocket_2.54mm:PinSocket_1x07_P2.54mm_Vertical","","1",""
"J13","NTC 10k (103AT-2)","Connector_JST:JST_PH_B2B-PH-K_1x02_P2.00mm_Vertical","B2B-PH-K-S","1",""
"J15","SW1 (cong tac roi >=3A)","Connector_JST:JST_XH_B2B-XH-A_1x02_P2.50mm_Vertical","B2B-XH-A","1",""
"L1","10uH 2A","Inductor_SMD:L_Taiyo-Yuden_NR-50xx","","1",""
"L2","1uH","Inductor_SMD:L_Vishay_IHLP-2525","IHLP2525CZER1R0M01","1",""
"L3","2.2uH 2.5A","Inductor_SMD:L_Changjiang_FNR4030S","","1",""
"L4","1.5uH","Inductor_SMD:L_Changjiang_FNR4020S","XFL4020-152ME","1",""
"Q1","DMG2305UX","Package_TO_SOT_SMD:SOT-23","DMG2305UX-7","1",""
"Q2","DMN2075U","Package_TO_SOT_SMD:SOT-23","DMN2075U-7","1",""
"Q3-Q5","2N7002","Package_TO_SOT_SMD:SOT-23","2N7002","3",""
"R1,R2,R11,R12,R16,R26,R54","100k","Resistor_SMD:R_0603_1608Metric","","7",""
"R3,R4","5.1k","Resistor_SMD:R_0603_1608Metric","","2",""
"R5","1.24k 1%","Resistor_SMD:R_0603_1608Metric","","1",""
"R6","1.91k 1%","Resistor_SMD:R_0603_1608Metric","","1",""
"R7","9.53k 1%","Resistor_SMD:R_0603_1608Metric","","1",""
"R8","511k 1%","Resistor_SMD:R_0603_1608Metric","","1",""
"R9,R29-R31,R50","10k","Resistor_SMD:R_0603_1608Metric","","5",""
"R10,R56","2.2k","Resistor_SMD:R_0603_1608Metric","","2",""
"R13","180k 0.1%","Resistor_SMD:R_0603_1608Metric","","1",""
"R14","11.1k 0.1%","Resistor_SMD:R_0603_1608Metric","","1",""
"R15","2.84M 0.1%","Resistor_SMD:R_0603_1608Metric","","1",""
"R17","68k","Resistor_SMD:R_0603_1608Metric","","1",""
"R18,R21,R23,R52","100k 1%","Resistor_SMD:R_0603_1608Metric","","4",""
"R19","13.3k 1%","Resistor_SMD:R_0603_1608Metric","","1",""
"R20","453k 1%","Resistor_SMD:R_0603_1608Metric","","1",""
"R22","649k 1%","Resistor_SMD:R_0603_1608Metric","","1",""
"R24","0R","Resistor_SMD:R_0603_1608Metric","","1",""
"R25","0R","Resistor_SMD:R_0603_1608Metric","","1","DNP"
"R27,R28","0.62R 1% 0.25W","Resistor_SMD:R_1206_3216Metric","","2",""
"R32","39.2k 1%","Resistor_SMD:R_0603_1608Metric","","1",""
"R33,R34","56k 1%","Resistor_SMD:R_0603_1608Metric","","2",""
"R35","470k","Resistor_SMD:R_0603_1608Metric","","1",""
"R36","4.7k","Resistor_SMD:R_0603_1608Metric","","1",""
"R37-R47,R55","1k","Resistor_SMD:R_0603_1608Metric","","12",""
"R48,R49","100","Resistor_SMD:R_0603_1608Metric","","2",""
"R51","20k","Resistor_SMD:R_0603_1608Metric","","1",""
"R53","27k 1%","Resistor_SMD:R_0603_1608Metric","","1",""
"U1","TLV6710","Package_TO_SOT_SMD:TSOT-23-6","TLV6710DDCR","1",""
"U2","TPS54302","Package_TO_SOT_SMD:SOT-23-6","TPS54302DDCR","1",""
"U3","TPS2553","Package_TO_SOT_SMD:SOT-23-6","TPS2553DBVR","1",""
"U4","TLV62569","Package_TO_SOT_SMD:SOT-23-5","TLV62569DBVR","1",""
"U5","SN74LVC1G08","Package_TO_SOT_SMD:SOT-23-5","SN74LVC1G08DBVR","1",""
"U6","DRV8833","Package_SO:HTSSOP-16-1EP_4.4x5mm_P0.65mm_EP3.4x5mm_Mask2.46x2.31mm_ThermalVias","DRV8833PWPR","1",""
"U7","BQ25886","Package_DFN_QFN:VQFN-24-1EP_4x4mm_P0.5mm_EP2.45x2.45mm","BQ25886RGER","1",""
"U8","TPS63070","mobot:Texas_RNM0015A_VQFN-15_2.5x3mm","TPS63070RNMR","1",""

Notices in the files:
README.md:
Rev B #5405, Feather ESP32-S3 #5323 (8 MB/no-PSRAM), Feather ESP32-S3 TFT #5483 (4 MB flash/2 MB PSRAM), Seeed Studio XIAO ESP32-S3 thường (STEP v2, CC BY-SA 4.0) và XIAO ESP32-C3 v1.3 (PCB KiCad, 68 footprint/47 package mesh tham khảo, bảng tra pad/net từ file PCB).
